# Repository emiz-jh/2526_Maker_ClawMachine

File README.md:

# **2526_Maker_ClawMachine**

##  **Description du Projet**
Dans le cadre de l'**Option Maker 2025-2026** à l'ENSEA, mon projet est de concevoir une machine à pince (Claw Machine) miniature.

L'idée est de concevoir un système automatisé capable de déplacer une pince sur trois axes (X, Y, Z) pour saisir et relâcher des objets.

## **Sommaire**
1. [Principe de réalisation](#1-principe-de-réalisation)
2. [Organisation du dépôt](#2-organisation-du-dépôt)
3. [Rétro-planning](#3-rétro-planning)

## **1. Principe de réalisation**
Pour mener à bien ce projet, j'utiliserais différentes technologies de prototypage rapide qu'on va étudier en cours :

### **1.1 Conception Mécanique & Fabrication**
* **Châssis (LASER) :** Conception d'une structure externe légère et rigide via la découpeuse LASER.
* **Système d'axes (3D Print) :** Déplacement X-Y-Z assuré par des rails et supports modélisés sur mesure et imprimés en 3D.
* **Pince motorisée :** Assemblage de pièces imprimées en 3D actionnées par un servomoteur.

### **1.2 Électronique & Énergie**
* **PCB :** Conception d'un circuit imprimé pour centraliser le contrôle des moteurs, du joystick et du bouton.
* **Alimentation (LiPo) :** Fabrication d'une alimentation avec un transformateur secteur vers 12V.

### **1.3 Gestion de projet & Livrables**
* **Versionning (Git) :** Utilisation de Git et GitHub pour le suivi du code source et des fichiers de conception.
* **Documentation :** Reporting sur ce README.md.
* **Rendu final :** Code source complet, fichiers de fabrication et vidéo de démonstration de 90 secondes.

## **2. Organisation du dépôt**

* **[Project_Management](./Project_Management/)** : Contient le suivi de projet, le journal de bord hebdomadaire, la to do list.
* **[CAD](./CAD)** : Plans de découpe LASER et modèles 3D (pince, supports, rails).
* **[Hardware](./Hardware)** : Schémas électriques, fichiers de routage du PCB et liste des composants (BOM).
* **[Software](./Software)** : Code source pour le pilotage des moteurs et la gestion des entrées utilisateur.
* **[Livrables](./Livrables)** : Exercices de la première partie de l'option Maker. 

## **3. La Vidéo**

**[Vidéo](./Video)** : 

La V2 améliorée avec effets et sous-titres:))
https://drive.google.com/file/d/1RBb7gfRtg3nFpQULt-ub-SjBEfwNZvmX/view?usp=sharing 
 
##
**Auteure :** Emilie ZHENG

**Encadrant :** Nicolas PAPAZOGLOU

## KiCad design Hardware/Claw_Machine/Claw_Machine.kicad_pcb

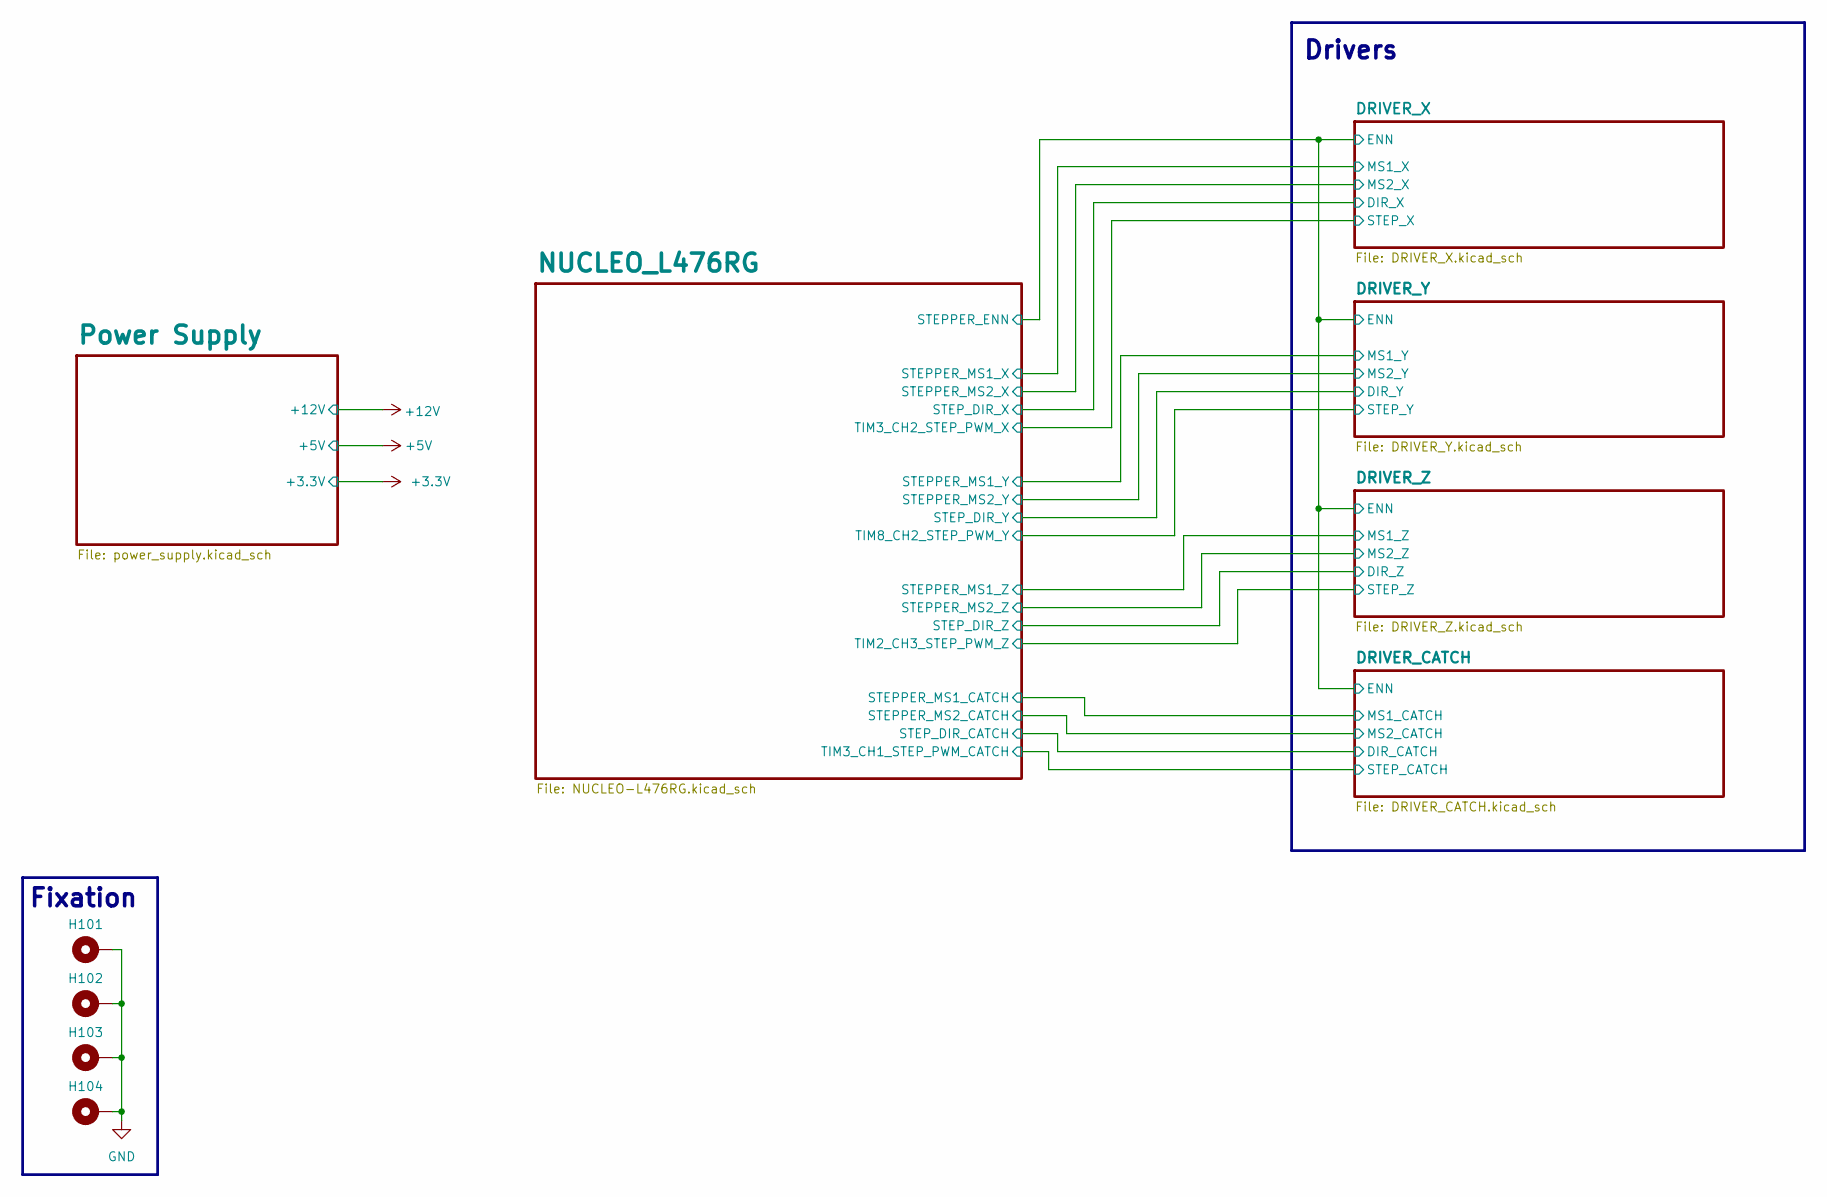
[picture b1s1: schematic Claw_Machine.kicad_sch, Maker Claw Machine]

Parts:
H101, H102, H103, H104: MountingHole_Pad; MountingHole_3.2mm_M3_Pad_Via

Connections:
GND: H101.1, H102.1, H103.1, H104.1; also elsewhere on the board

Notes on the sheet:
Fixation
Drivers

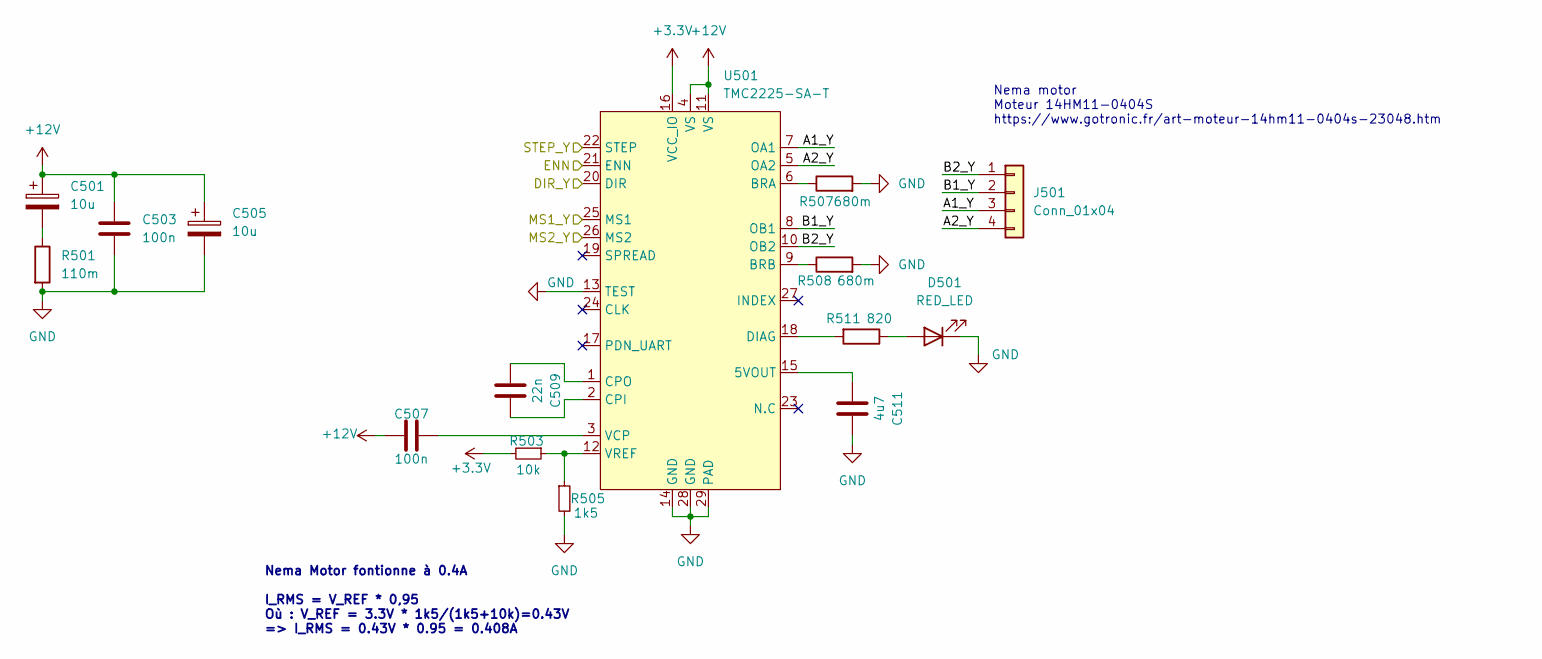
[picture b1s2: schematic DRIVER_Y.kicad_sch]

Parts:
C501, C505: 10u; CP_Elec_4x5.7; MPN WE 865060440001
C503, C507: 100n; C_0402_1005Metric; MPN WE 885012105018
C509: 22n; C_0402_1005Metric; MPN WE 885012205052
C511: 4u7; C_0402_1005Metric; MPN WE 885012105008
D501: RED_LED; LED_0603_1608Metric; MPN WE 150060RS55040
J501: Conn_01x04; JST_XH_B4B-XH-A_1x04_P2.50mm_Vertical; MPN S4B-XH-A(lf)(sn)
R501: 110m; R_0603_1608Metric_Pad0.98x0.95mm_HandSolder; MPN MFL0603R1100FB
R503: 10k; R_0402_1005Metric
R505: 1k5; R_0805_2012Metric_Pad1.20x1.40mm_HandSolder
R507, R508: 680m; R_1206_3216Metric_Pad1.30x1.75mm_HandSolder; MPN WW12PR680FTL
R511: 820; R_0402_1005Metric
U501: TMC2225-SA-T; HTSSOP-28-1EP_4.4x9.7mm_P0.65mm_EP2.85x5.4mm_ThermalVias; MPN TMC2225-SA-T

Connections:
+3.3V: R503.2, U501.16 (VCC_IO); also elsewhere on the board
+12V: C501.1, C503.1, C505.1, C507.1, U501.4 (VS), U501.11 (VS); also elsewhere on the board
/DRIVER_CATCH/ENN: U501.21 (ENN); also elsewhere on the board
/DRIVER_Y/A1_Y: J501.3, U501.7 (OA1)
/DRIVER_Y/A2_Y: J501.4, U501.5 (OA2)
/DRIVER_Y/B1_Y: J501.2, U501.8 (OB1)
/DRIVER_Y/B2_Y: J501.1, U501.10 (OB2)
/DRIVER_Y/DIR_Y: U501.20 (DIR); also elsewhere on the board
/DRIVER_Y/MS1_Y: U501.25 (MS1); also elsewhere on the board
/DRIVER_Y/MS2_Y: U501.26 (MS2); also elsewhere on the board
/DRIVER_Y/STEP_Y: U501.22 (STEP); also elsewhere on the board
GND: C503.2, C505.2, C511.1, D501.1 (K), R501.2, R505.2, R507.2, R508.2, U501.13 (TEST), U501.14 (GND), U501.28 (GND), U501.29 (PAD); also elsewhere on the board
unnamed: C501.2, R501.1
unnamed: D501.2 (A), R511.1
unnamed: C511.2, U501.15 (5VOUT)
unnamed: R507.1, U501.6 (BRA)
unnamed: R508.1, U501.9 (BRB)
unnamed: C509.1, U501.2 (CPI)
unnamed: C509.2, U501.1 (CPO)
unnamed: R511.2, U501.18 (DIAG)
unnamed: C507.2, U501.3 (VCP)
unnamed: R503.1, R505.1, U501.12 (VREF)

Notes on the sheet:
Nema motor Moteur 14HM11-0404S https://www.gotronic.fr/art-moteur-14hm11-0404s-23048.htm
Nema Motor fontionne à 0.4A I_RMS = V_REF * 0,95 Où : V_REF = 3.3V * 1k5/(1k5+10k)=0.43V => I_RMS = 0.43V * 0.95 = 0.408A

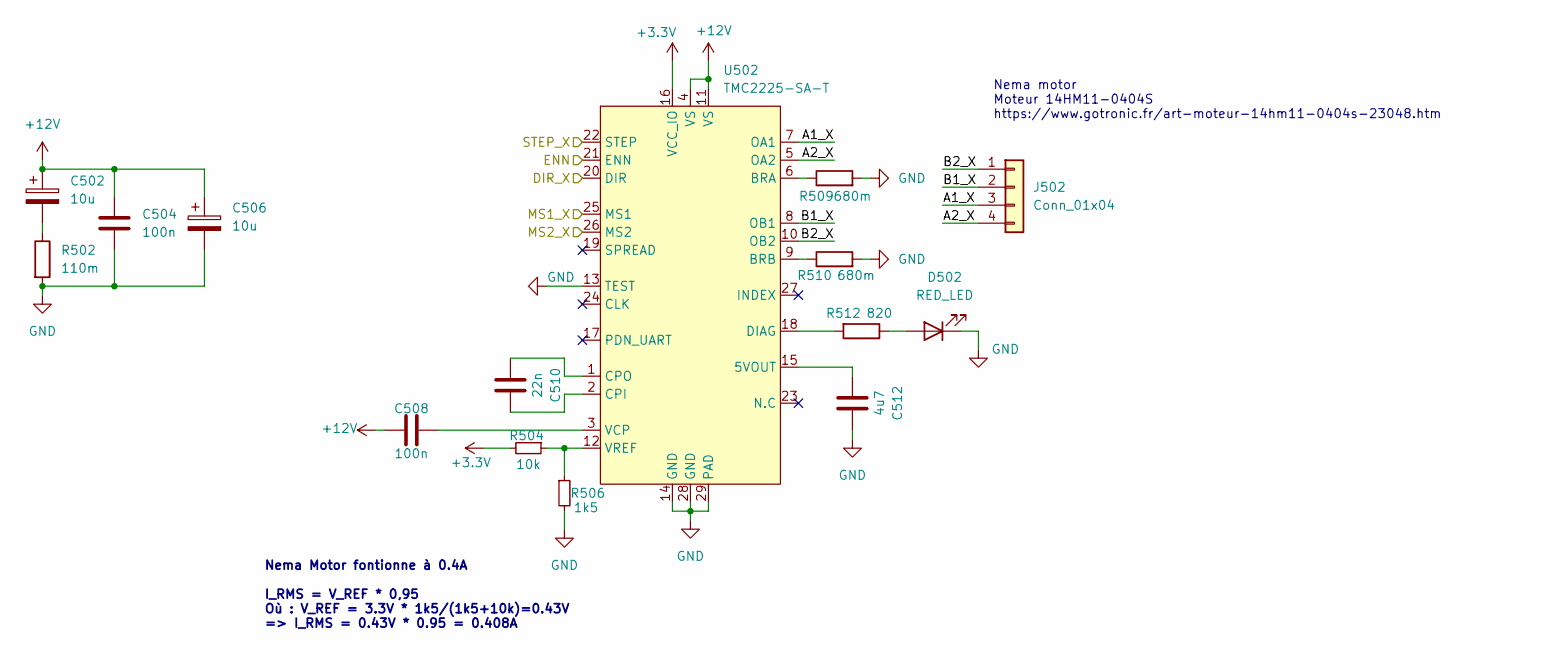
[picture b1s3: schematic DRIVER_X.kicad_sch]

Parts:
C502, C506: 10u; CP_Elec_4x5.7; MPN WE 865060440001
C504, C508: 100n; C_0402_1005Metric; MPN WE 885012105018
C510: 22n; C_0402_1005Metric; MPN WE 885012205052
C512: 4u7; C_0402_1005Metric; MPN WE 885012105008
D502: RED_LED; LED_0603_1608Metric; MPN WE 150060RS55040
J502: Conn_01x04; JST_XH_B4B-XH-A_1x04_P2.50mm_Vertical; MPN S4B-XH-A(lf)(sn)
R502: 110m; R_0603_1608Metric_Pad0.98x0.95mm_HandSolder; MPN MFL0603R1100FB
R504: 10k; R_0402_1005Metric
R506: 1k5; R_0805_2012Metric_Pad1.20x1.40mm_HandSolder
R509, R510: 680m; R_1206_3216Metric_Pad1.30x1.75mm_HandSolder; MPN WW12PR680FTL
R512: 820; R_0402_1005Metric
U502: TMC2225-SA-T; HTSSOP-28-1EP_4.4x9.7mm_P0.65mm_EP2.85x5.4mm_ThermalVias; MPN TMC2225-SA-T

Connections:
+3.3V: R504.2, U502.16 (VCC_IO); also elsewhere on the board
+12V: C502.1, C504.1, C506.1, C508.1, U502.4 (VS), U502.11 (VS); also elsewhere on the board
/DRIVER_CATCH/ENN: U502.21 (ENN); also elsewhere on the board
/DRIVER_X/A1_X: J502.3, U502.7 (OA1)
/DRIVER_X/A2_X: J502.4, U502.5 (OA2)
/DRIVER_X/B1_X: J502.2, U502.8 (OB1)
/DRIVER_X/B2_X: J502.1, U502.10 (OB2)
/DRIVER_X/DIR_X: U502.20 (DIR); also elsewhere on the board
/DRIVER_X/MS1_X: U502.25 (MS1); also elsewhere on the board
/DRIVER_X/MS2_X: U502.26 (MS2); also elsewhere on the board
/DRIVER_X/STEP_X: U502.22 (STEP); also elsewhere on the board
GND: C504.2, C506.2, C512.1, D502.1 (K), R502.2, R506.2, R509.2, R510.2, U502.13 (TEST), U502.14 (GND), U502.28 (GND), U502.29 (PAD); also elsewhere on the board
unnamed: C502.2, R502.1
unnamed: D502.2 (A), R512.1
unnamed: C512.2, U502.15 (5VOUT)
unnamed: R509.1, U502.6 (BRA)
unnamed: R510.1, U502.9 (BRB)
unnamed: C510.1, U502.2 (CPI)
unnamed: C510.2, U502.1 (CPO)
unnamed: R512.2, U502.18 (DIAG)
unnamed: C508.2, U502.3 (VCP)
unnamed: R504.1, R506.1, U502.12 (VREF)

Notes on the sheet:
Nema motor Moteur 14HM11-0404S https://www.gotronic.fr/art-moteur-14hm11-0404s-23048.htm
Nema Motor fontionne à 0.4A I_RMS = V_REF * 0,95 Où : V_REF = 3.3V * 1k5/(1k5+10k)=0.43V => I_RMS = 0.43V * 0.95 = 0.408A

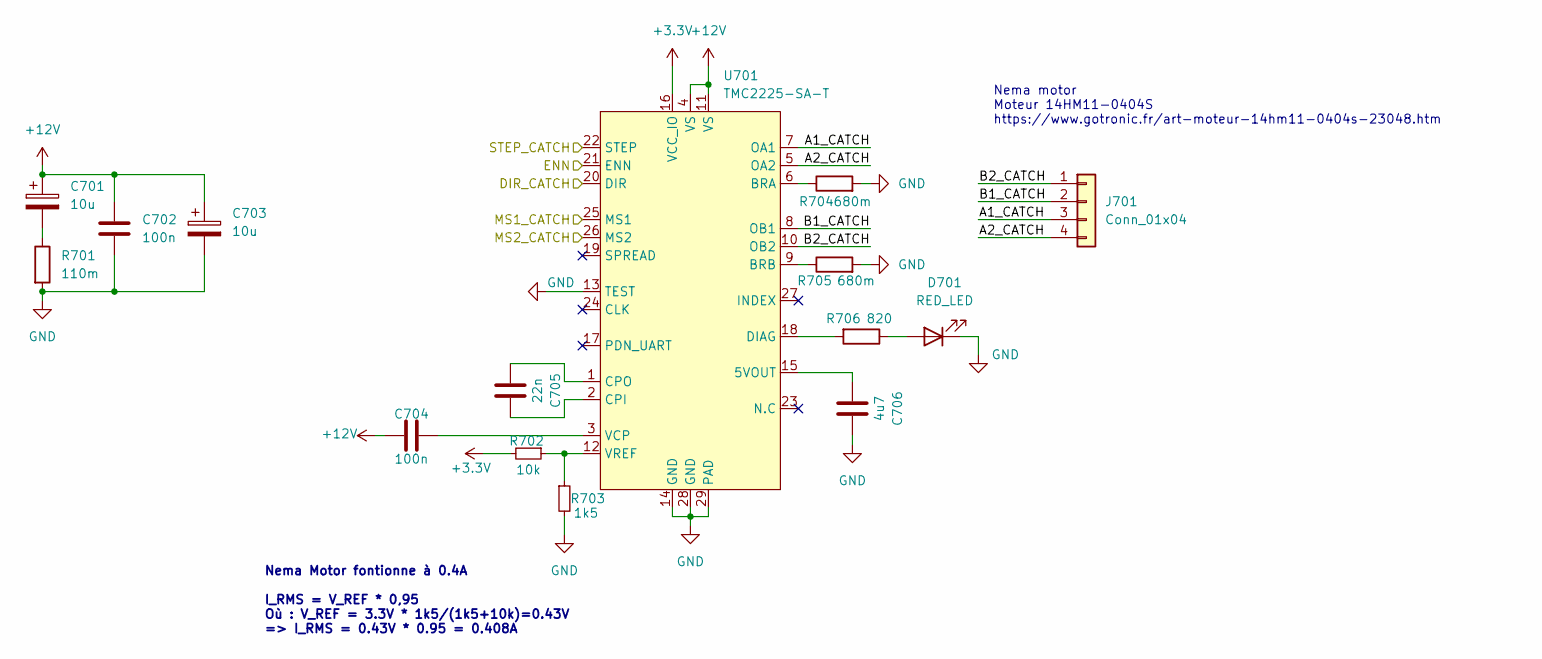
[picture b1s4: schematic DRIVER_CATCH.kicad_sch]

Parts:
C701, C703: 10u; CP_Elec_4x5.7; MPN WE 865060440001
C702, C704: 100n; C_0402_1005Metric; MPN WE 885012105018
C705: 22n; C_0402_1005Metric; MPN WE 885012205052
C706: 4u7; C_0402_1005Metric; MPN WE 885012105008
D701: RED_LED; LED_0603_1608Metric; MPN WE 150060RS55040
J701: Conn_01x04; JST_XH_B4B-XH-A_1x04_P2.50mm_Vertical; MPN S4B-XH-A(lf)(sn)
R701: 110m; R_0603_1608Metric_Pad0.98x0.95mm_HandSolder; MPN MFL0603R1100FB
R702: 10k; R_0402_1005Metric
R703: 1k5; R_0805_2012Metric_Pad1.20x1.40mm_HandSolder
R704, R705: 680m; R_1206_3216Metric_Pad1.30x1.75mm_HandSolder; MPN WW12PR680FTL
R706: 820; R_0402_1005Metric
U701: TMC2225-SA-T; HTSSOP-28-1EP_4.4x9.7mm_P0.65mm_EP2.85x5.4mm_ThermalVias; MPN TMC2225-SA-T

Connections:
+3.3V: R702.2, U701.16 (VCC_IO); also elsewhere on the board
+12V: C701.1, C702.1, C703.1, C704.1, U701.4 (VS), U701.11 (VS); also elsewhere on the board
/DRIVER_CATCH/A1_CATCH: J701.3, U701.7 (OA1)
/DRIVER_CATCH/A2_CATCH: J701.4, U701.5 (OA2)
/DRIVER_CATCH/B1_CATCH: J701.2, U701.8 (OB1)
/DRIVER_CATCH/B2_CATCH: J701.1, U701.10 (OB2)
/DRIVER_CATCH/DIR_CATCH: U701.20 (DIR); also elsewhere on the board
/DRIVER_CATCH/ENN: U701.21 (ENN); also elsewhere on the board
/DRIVER_CATCH/MS1_CATCH: U701.25 (MS1); also elsewhere on the board
/DRIVER_CATCH/MS2_CATCH: U701.26 (MS2); also elsewhere on the board
/DRIVER_CATCH/STEP_CATCH: U701.22 (STEP); also elsewhere on the board
GND: C702.2, C703.2, C706.1, D701.1 (K), R701.2, R703.2, R704.2, R705.2, U701.13 (TEST), U701.14 (GND), U701.28 (GND), U701.29 (PAD); also elsewhere on the board
unnamed: C701.2, R701.1
unnamed: D701.2 (A), R706.1
unnamed: C706.2, U701.15 (5VOUT)
unnamed: R704.1, U701.6 (BRA)
unnamed: R705.1, U701.9 (BRB)
unnamed: C705.1, U701.2 (CPI)
unnamed: C705.2, U701.1 (CPO)
unnamed: R706.2, U701.18 (DIAG)
unnamed: C704.2, U701.3 (VCP)
unnamed: R702.1, R703.1, U701.12 (VREF)

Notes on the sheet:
Nema Motor fontionne à 0.4A I_RMS = V_REF * 0,95 Où : V_REF = 3.3V * 1k5/(1k5+10k)=0.43V => I_RMS = 0.43V * 0.95 = 0.408A
Nema motor Moteur 14HM11-0404S https://www.gotronic.fr/art-moteur-14hm11-0404s-23048.htm

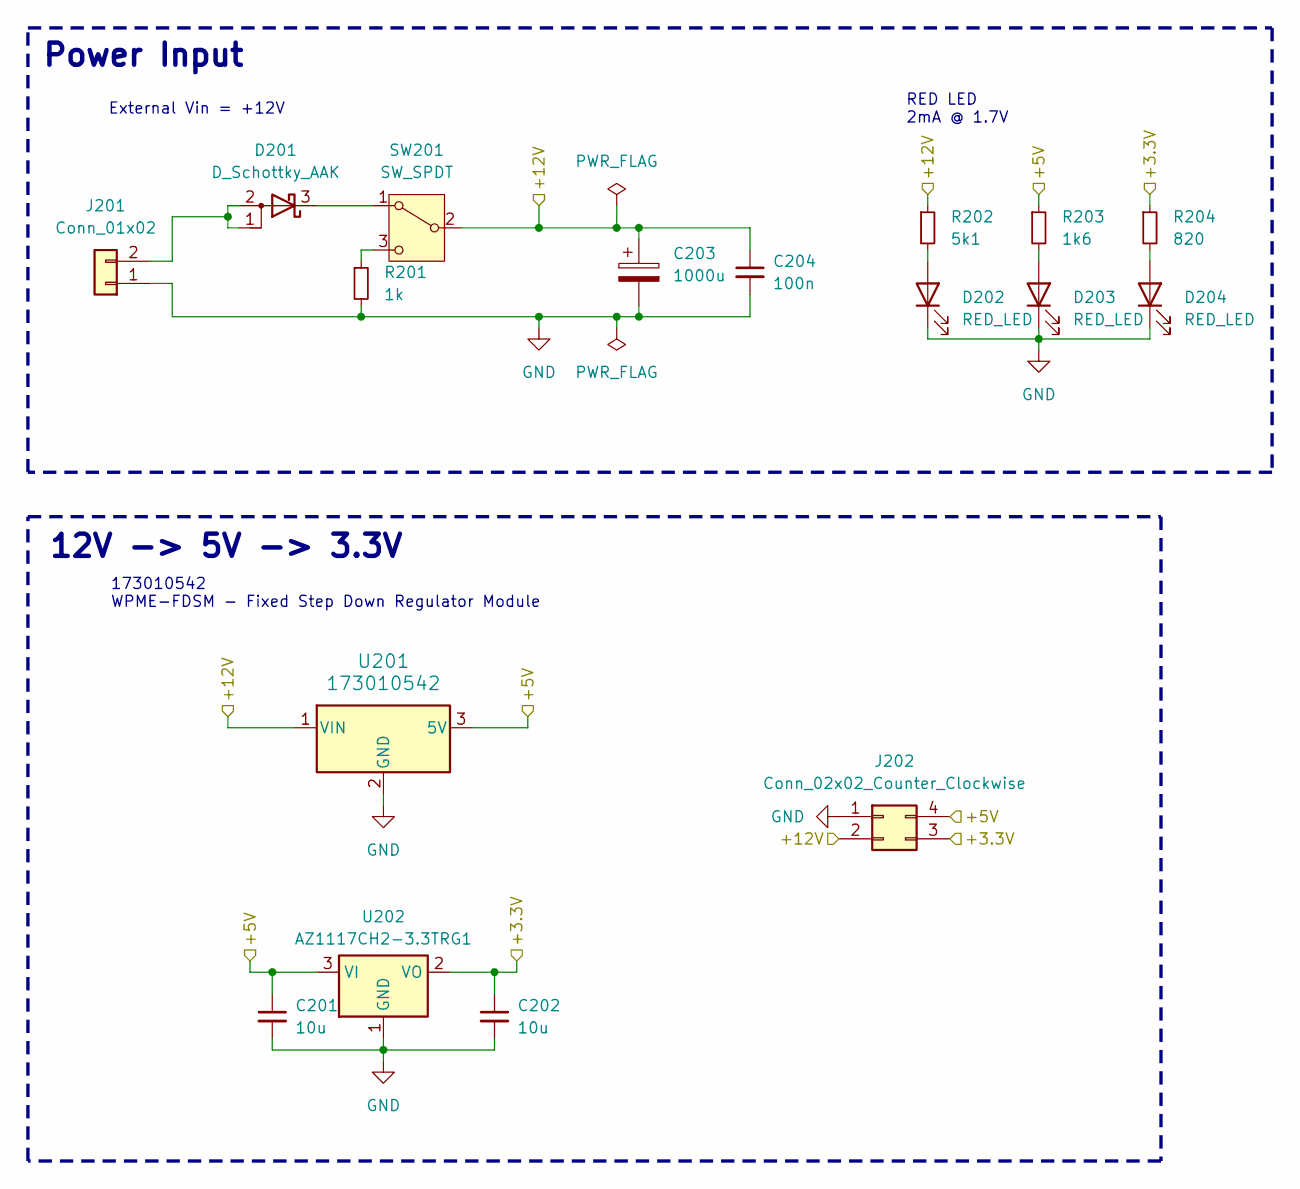
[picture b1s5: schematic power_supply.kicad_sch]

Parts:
C201, C202: 10u; C_0402_1005Metric; MPN WE 885012105020
C203: 1000u; CP_Elec_5x5.4; MPN WE 865060442002
C204: 100n; C_0603_1608Metric; MPN WE 885012105018
D201: D_Schottky_AAK; DST10100S
D202, D203, D204: RED_LED; LED_0603_1608Metric; MPN WE 150060RS55040
J201: Conn_01x02; AMASS_XT30U-M_1x02_P5.0mm_Vertical
J202: Conn_02x02_Counter_Clockwise; PinHeader_2x02_P2.54mm_Vertical_SMD; MPN WE 61000421121
R201: 1k; R_0805_2012Metric
R202: 5k1; R_0402_1005Metric
R203: 1k6; R_0402_1005Metric
R204: 820; R_0402_1005Metric
SW201: SW_SPDT; 472121020311_bis; MPN WE 472121020311
U201: 173010542; WPME-FDSM_173010X42; MPN WE 173010542
U202: AZ1117CH2-3.3TRG1; SOT-223-3_TabPin2; MPN AZ1117CH2-3.3TRG1

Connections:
+3.3V: C202.1, J202.3, R204.1, U202.2 (VO); also elsewhere on the board
+5V: C201.1, J202.4, R203.1, U201.3 (5V), U202.3 (VI); also elsewhere on the board
+12V: C203.1, C204.1, J202.2, R202.1, SW201.2 (B), U201.1 (VIN); also elsewhere on the board
GND: C201.2, C202.2, C203.2, C204.2, D202.1 (K), D203.1 (K), D204.1 (K), J201.1, J202.1, R201.2, U201.2 (GND), U202.1 (GND); also elsewhere on the board
unnamed: D201.3 (K), SW201.1 (A)
unnamed: D202.2 (A), R202.2
unnamed: D203.2 (A), R203.2
unnamed: D204.2 (A), R204.2
unnamed: D201.1 (A), D201.2 (A), J201.2
unnamed: R201.1, SW201.3 (C)

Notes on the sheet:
External Vin = +12V
Power Input
RED LED 2mA @ 1.7V
12V -> 5V -> 3.3V
173010542 WPME-FDSM - Fixed Step Down Regulator Module

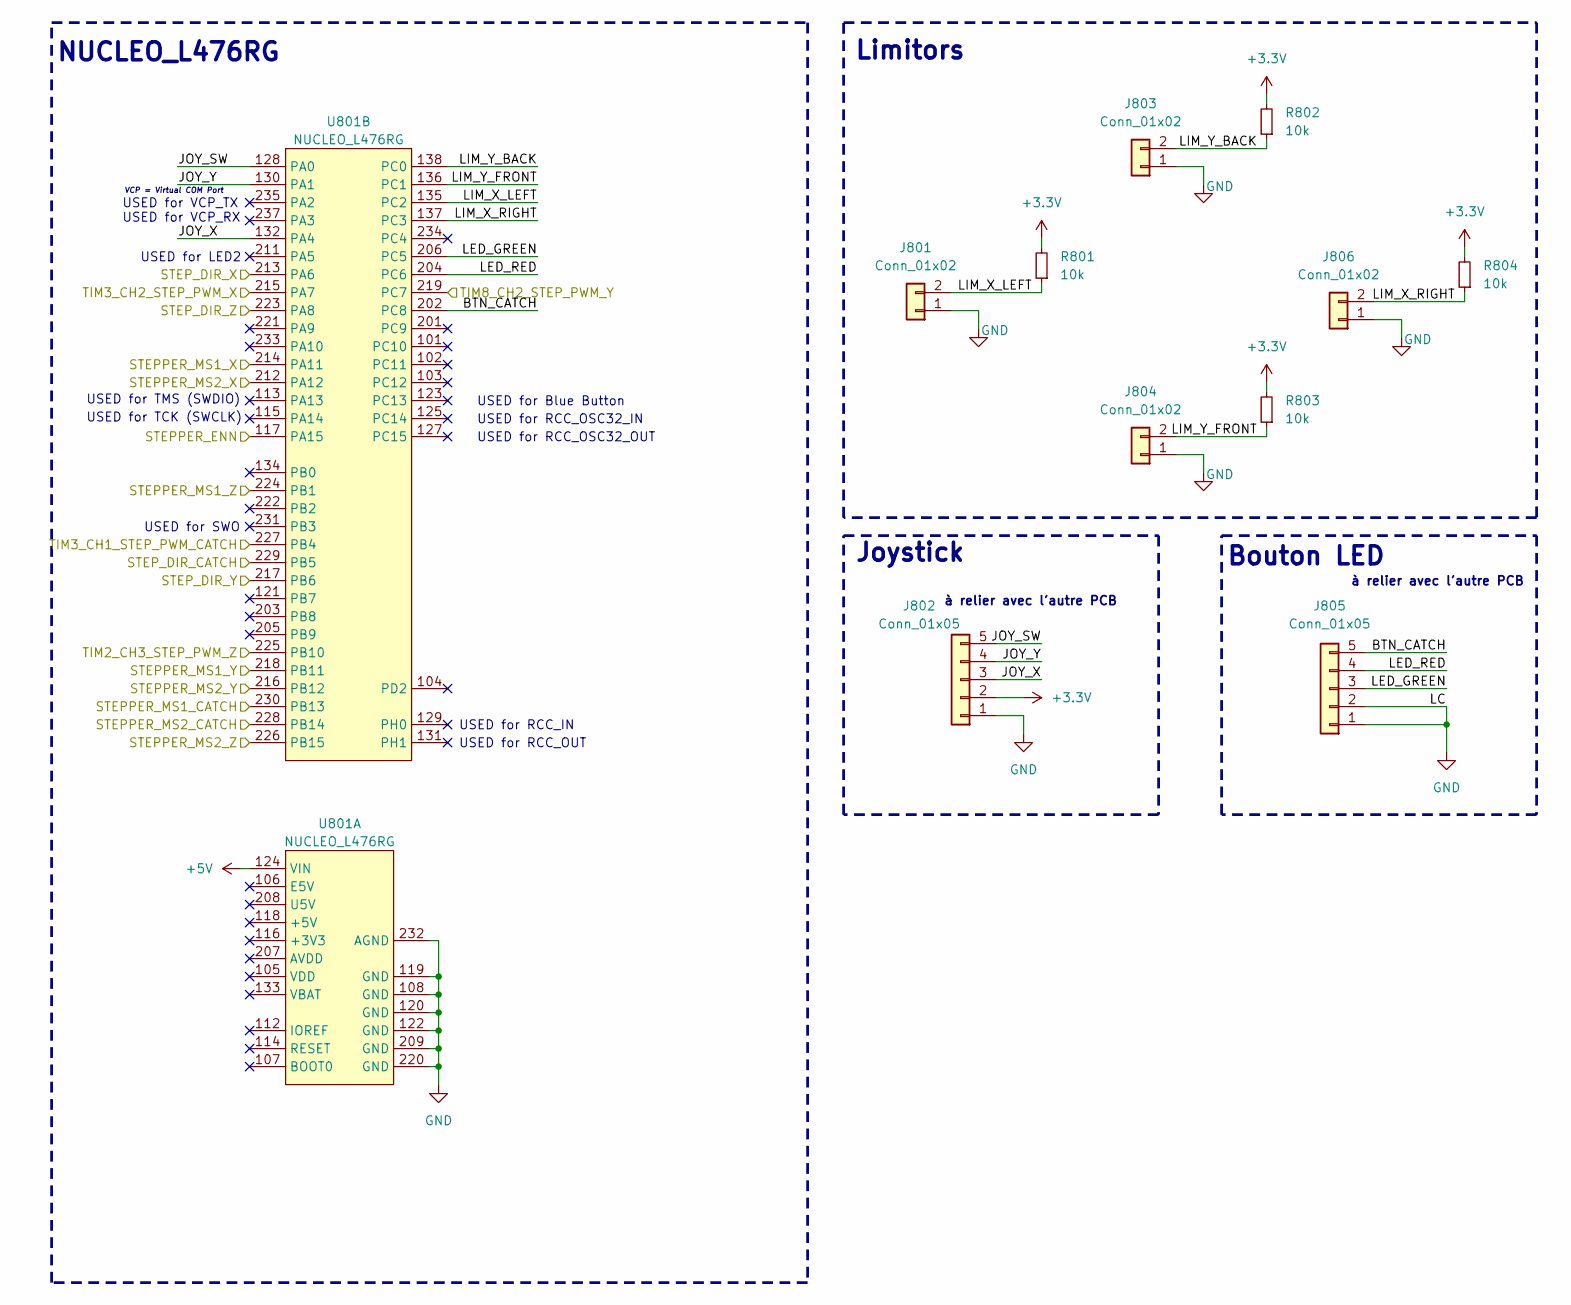
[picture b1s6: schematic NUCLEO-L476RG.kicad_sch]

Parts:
J801, J803, J804, J806: Conn_01x02; JST_EH_B2B-EH-A_1x02_P2.50mm_Vertical
J802, J805: Conn_01x05; JST_XH_B5B-XH-A_1x05_P2.50mm_Vertical
R801, R802, R803, R804: 10k; R_0402_1005Metric
U801: NUCLEO_L476RG; ST_NUCLEO_64; MPN TSW-119-19-T-D

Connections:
+3.3V: J802.2, R801.2, R802.2, R803.2, R804.2; also elsewhere on the board
+5V: U801.124 (VIN); also elsewhere on the board
/DRIVER_CATCH/DIR_CATCH: U801.229 (PB5); also elsewhere on the board
/DRIVER_CATCH/ENN: U801.117 (PA15); also elsewhere on the board
/DRIVER_CATCH/MS1_CATCH: U801.230 (PB13); also elsewhere on the board
/DRIVER_CATCH/MS2_CATCH: U801.228 (PB14); also elsewhere on the board
/DRIVER_CATCH/STEP_CATCH: U801.227 (PB4); also elsewhere on the board
/DRIVER_X/DIR_X: U801.213 (PA6); also elsewhere on the board
/DRIVER_X/MS1_X: U801.214 (PA11); also elsewhere on the board
/DRIVER_X/MS2_X: U801.212 (PA12); also elsewhere on the board
/DRIVER_X/STEP_X: U801.215 (PA7); also elsewhere on the board
/DRIVER_Y/DIR_Y: U801.217 (PB6); also elsewhere on the board
/DRIVER_Y/MS1_Y: U801.218 (PB11); also elsewhere on the board
/DRIVER_Y/MS2_Y: U801.216 (PB12); also elsewhere on the board
/DRIVER_Y/STEP_Y: U801.219 (PC7); also elsewhere on the board
/DRIVER_Z/DIR_Z: U801.223 (PA8); also elsewhere on the board
/DRIVER_Z/MS1_Z: U801.224 (PB1); also elsewhere on the board
/DRIVER_Z/MS2_Z: U801.226 (PB15); also elsewhere on the board
/DRIVER_Z/STEP_Z: U801.225 (PB10); also elsewhere on the board
/NUCLEO_L476RG/BTN_CATCH: J805.5, U801.202 (PC8)
/NUCLEO_L476RG/JOY_SW: J802.5, U801.128 (PA0)
/NUCLEO_L476RG/JOY_X: J802.3, U801.132 (PA4)
/NUCLEO_L476RG/JOY_Y: J802.4, U801.130 (PA1)
/NUCLEO_L476RG/LED_GREEN: J805.3, U801.206 (PC5)
/NUCLEO_L476RG/LED_RED: J805.4, U801.204 (PC6)
/NUCLEO_L476RG/LIM_X_LEFT: J801.2, R801.1, U801.135 (PC2)
/NUCLEO_L476RG/LIM_X_RIGHT: J806.2, R804.1, U801.137 (PC3)
/NUCLEO_L476RG/LIM_Y_BACK: J803.2, R802.1, U801.138 (PC0)
/NUCLEO_L476RG/LIM_Y_FRONT: J804.2, R803.1, U801.136 (PC1)
GND: J801.1, J802.1, J803.1, J804.1, J805.1, J805.2, J806.1, U801.108 (GND), U801.119 (GND), U801.120 (GND), U801.122 (GND), U801.209 (GND), U801.220 (GND), U801.232 (AGND); also elsewhere on the board

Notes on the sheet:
USED for VCP_TX
Limitors
USED for RCC_OSC32_OUT
USED for Blue Button
USED for TMS (SWDIO)
USED for VCP_RX
USED for RCC_IN
NUCLEO_L476RG
USED for RCC_OUT
Bouton LED
USED for SWO
USED for TCK (SWCLK)
USED for LED2
USED for RCC_OSC32_IN
Joystick
VCP = Virtual COM Port
à relier avec l'autre PCB

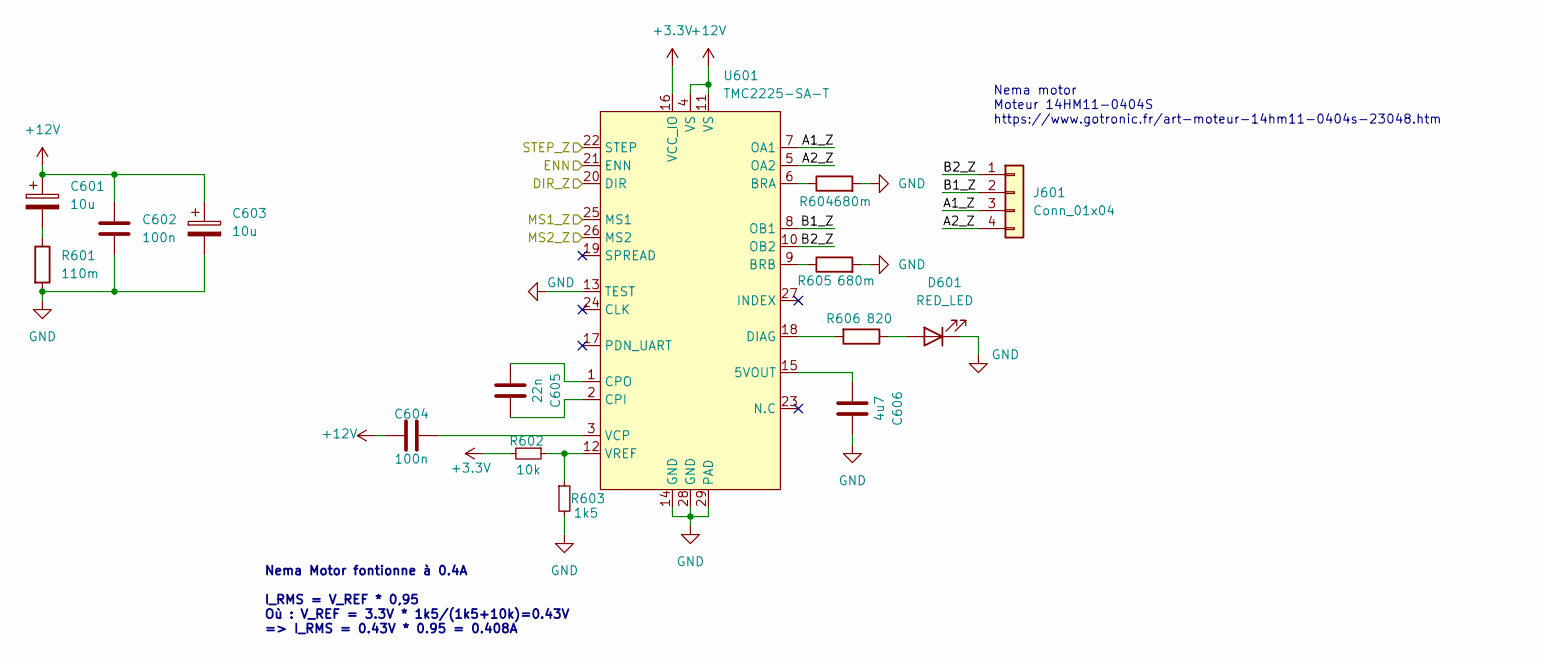
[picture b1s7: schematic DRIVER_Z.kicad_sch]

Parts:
C601, C603: 10u; CP_Elec_4x5.7; MPN WE 865060440001
C602, C604: 100n; C_0402_1005Metric; MPN WE 885012105018
C605: 22n; C_0402_1005Metric; MPN WE 885012205052
C606: 4u7; C_0402_1005Metric; MPN WE 885012105008
D601: RED_LED; LED_0603_1608Metric; MPN WE 150060RS55040
J601: Conn_01x04; JST_XH_B4B-XH-A_1x04_P2.50mm_Vertical; MPN S4B-XH-A(lf)(sn)
R601: 110m; R_0603_1608Metric_Pad0.98x0.95mm_HandSolder; MPN MFL0603R1100FB
R602: 10k; R_0402_1005Metric
R603: 1k5; R_0805_2012Metric_Pad1.20x1.40mm_HandSolder
R604, R605: 680m; R_1206_3216Metric_Pad1.30x1.75mm_HandSolder; MPN WW12PR680FTL
R606: 820; R_0402_1005Metric
U601: TMC2225-SA-T; HTSSOP-28-1EP_4.4x9.7mm_P0.65mm_EP2.85x5.4mm_ThermalVias; MPN TMC2225-SA-T

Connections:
+3.3V: R602.2, U601.16 (VCC_IO); also elsewhere on the board
+12V: C601.1, C602.1, C603.1, C604.1, U601.4 (VS), U601.11 (VS); also elsewhere on the board
/DRIVER_CATCH/ENN: U601.21 (ENN); also elsewhere on the board
/DRIVER_Z/A1_Z: J601.3, U601.7 (OA1)
/DRIVER_Z/A2_Z: J601.4, U601.5 (OA2)
/DRIVER_Z/B1_Z: J601.2, U601.8 (OB1)
/DRIVER_Z/B2_Z: J601.1, U601.10 (OB2)
/DRIVER_Z/DIR_Z: U601.20 (DIR); also elsewhere on the board
/DRIVER_Z/MS1_Z: U601.25 (MS1); also elsewhere on the board
/DRIVER_Z/MS2_Z: U601.26 (MS2); also elsewhere on the board
/DRIVER_Z/STEP_Z: U601.22 (STEP); also elsewhere on the board
GND: C602.2, C603.2, C606.1, D601.1 (K), R601.2, R603.2, R604.2, R605.2, U601.13 (TEST), U601.14 (GND), U601.28 (GND), U601.29 (PAD); also elsewhere on the board
unnamed: C601.2, R601.1
unnamed: D601.2 (A), R606.1
unnamed: C606.2, U601.15 (5VOUT)
unnamed: R604.1, U601.6 (BRA)
unnamed: R605.1, U601.9 (BRB)
unnamed: C605.1, U601.2 (CPI)
unnamed: C605.2, U601.1 (CPO)
unnamed: R606.2, U601.18 (DIAG)
unnamed: C604.2, U601.3 (VCP)
unnamed: R602.1, R603.1, U601.12 (VREF)

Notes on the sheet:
Nema Motor fontionne à 0.4A I_RMS = V_REF * 0,95 Où : V_REF = 3.3V * 1k5/(1k5+10k)=0.43V => I_RMS = 0.43V * 0.95 = 0.408A
Nema motor Moteur 14HM11-0404S https://www.gotronic.fr/art-moteur-14hm11-0404s-23048.htm

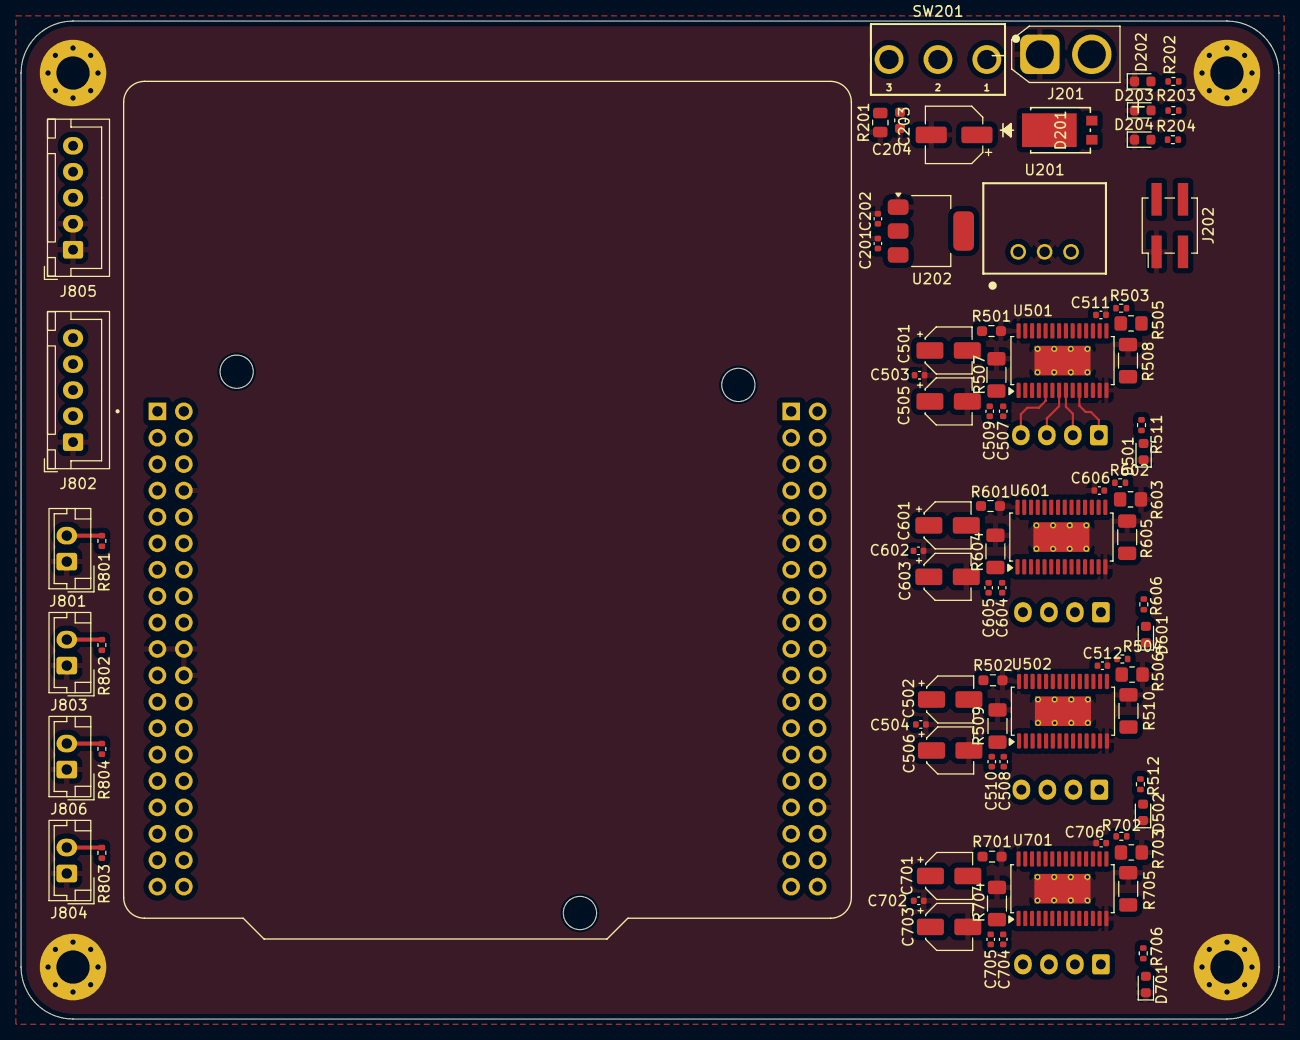
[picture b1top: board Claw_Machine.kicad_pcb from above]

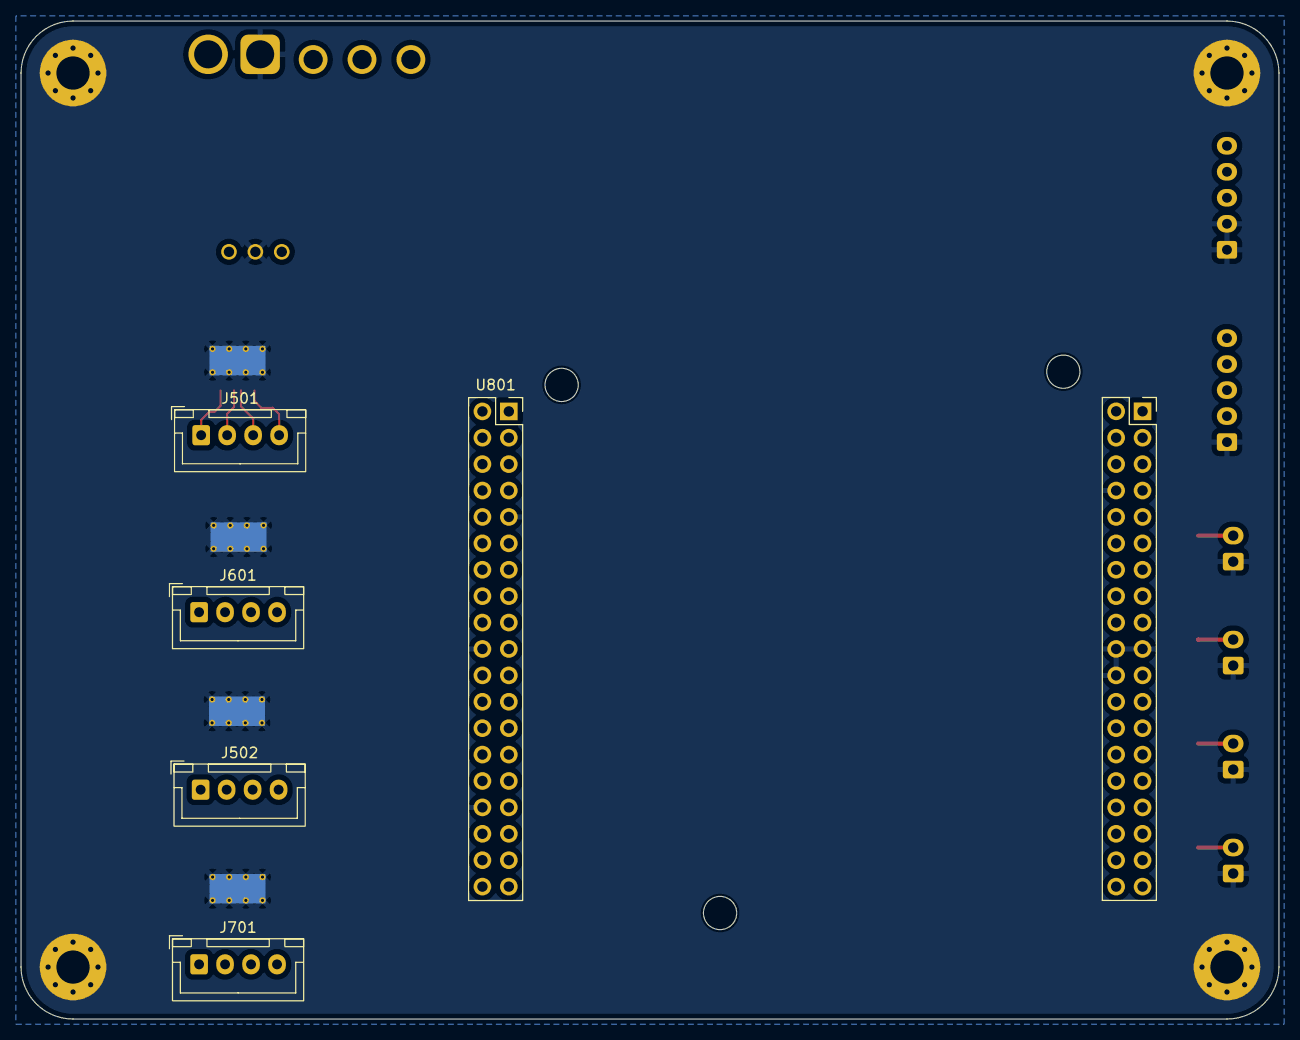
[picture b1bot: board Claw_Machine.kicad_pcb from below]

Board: 4 copper layers, 121.0 x 96.0 mm, 92 parts (4 on the bottom side), 93 nets.

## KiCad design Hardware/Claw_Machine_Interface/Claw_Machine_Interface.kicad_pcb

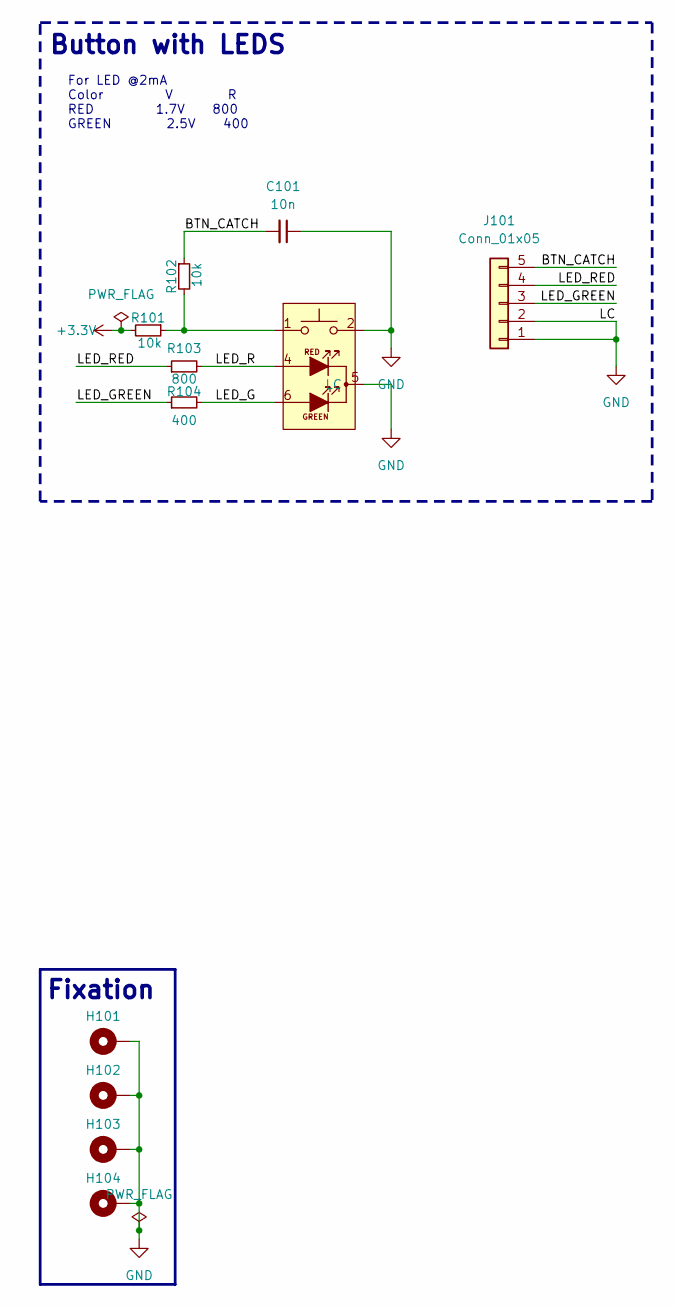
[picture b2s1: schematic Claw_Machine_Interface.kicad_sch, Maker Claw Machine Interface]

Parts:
Bouton_LED101: 465RG11172501_bis
C101: 10n; C_0603_1608Metric; MPN WE 885012205050
H101, H102, H103, H104: MountingHole_Pad; MountingHole_3.2mm_M3_Pad_Via
J101: Conn_01x05; JST_XH_B5B-XH-A_1x05_P2.50mm_Vertical
R101, R102: 10k; R_0603_1608Metric
R103: 800; R_0603_1608Metric
R104: 400; R_0603_1608Metric

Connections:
+3.3V: R101.2
/BTN_CATCH: C101.2, J101.5, R102.1
/LED_G: Bouton_LED101.6, R104.2; also elsewhere on the board
/LED_GREEN: J101.3, R104.1
/LED_R: Bouton_LED101.4, R103.2; also elsewhere on the board
/LED_RED: J101.4, R103.1
GND: Bouton_LED101.2, Bouton_LED101.5 (LC), C101.1, H101.1, H102.1, H103.1, H104.1, J101.1, J101.2; also elsewhere on the board
unnamed 7: Bouton_LED101.1, R101.1, R102.2; also elsewhere on the board

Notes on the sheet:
For LED @2mA Color V R RED 1.7V 800 GREEN 2.5V 400
Fixation
Button with LEDS
